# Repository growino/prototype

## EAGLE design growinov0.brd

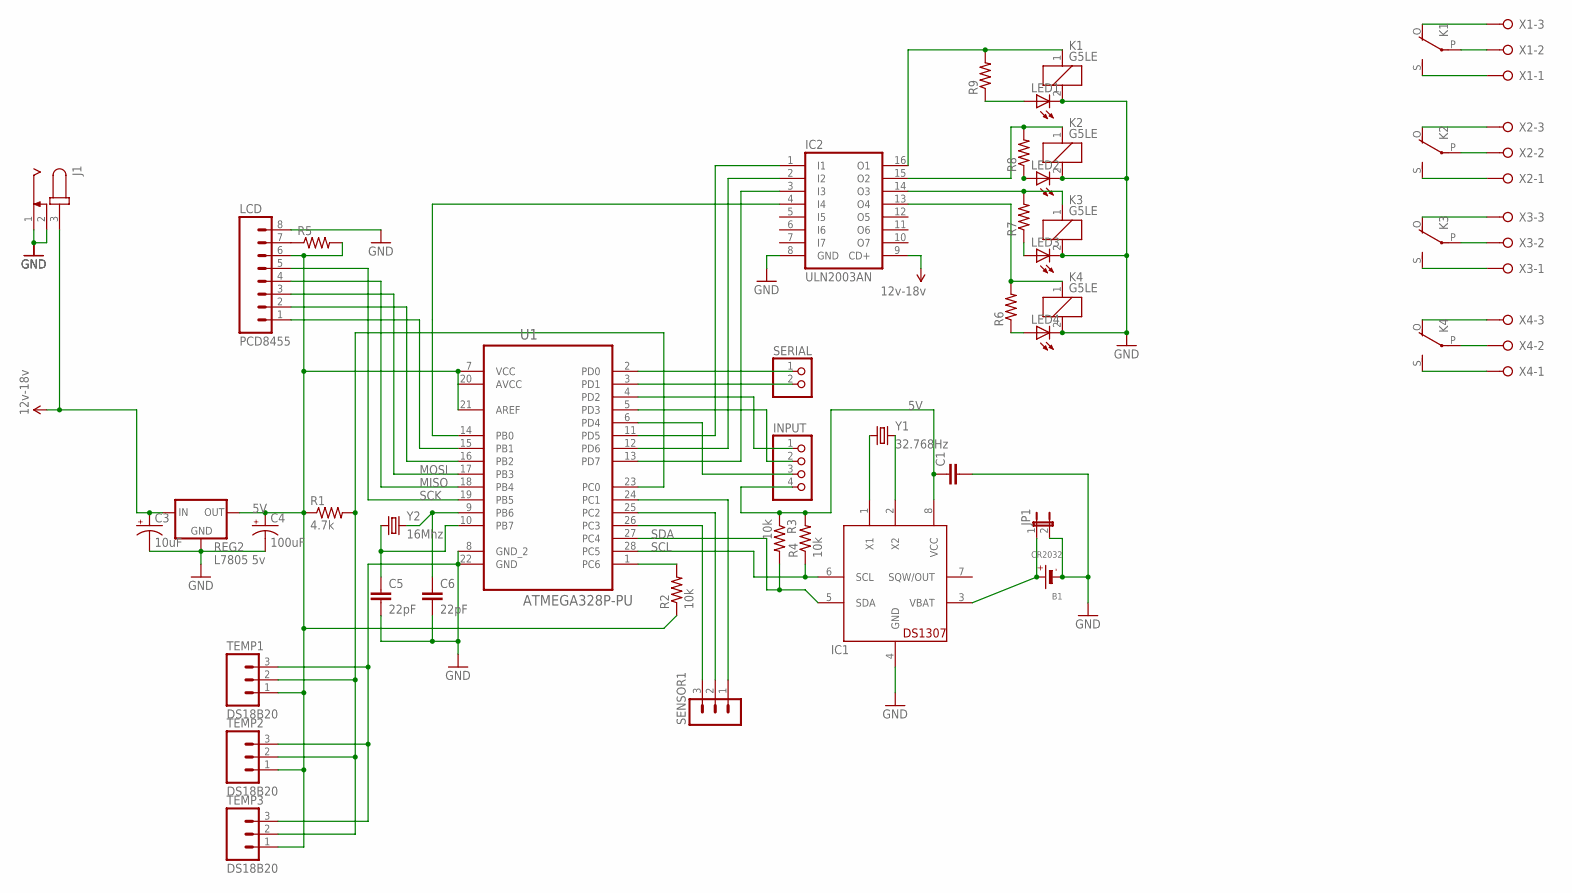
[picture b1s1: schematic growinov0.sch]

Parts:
B1: CR2032
C1: CAPPTH1; CAP-PTH-5MM
C3: 10uF; CPOL-RADIAL-10UF-25V
C4: 100uF; CPOL-RADIAL-100UF-25V
C5, C6: 22pF; CAP-PTH-SMALL-KIT
IC1: DS1307; DIL08
IC2: ULN2003AN; DIL16
INPUT: PINHD-1X4; 1X04
J1: JACK-PLUG0; SPC4077
JP1: JUMPER-2PTH; 1X02
K1, K2, K3, K4: G5LE
LCD: PCD8455; 1X08
LED1, LED2, LED3, LED4: LED3MM
R1: 4.7k; AXIAL-0.4
R2, R3, R4: 10k; AXIAL-0.4
R5, R6, R7, R8, R9: RESISTORPTH-1/4W-VERT; AXIAL-0.1
REG2: L7805 5v; 78XXL
SENSOR1: MA03-1
SERIAL: PINHD-1X2; 1X02
TEMP1, TEMP2, TEMP3: DS18B20; MOLEX-1X3
U1: ATMEGA328P-PU; DIP254P762X457-28
X1, X2, X3, X4: W237-3E
Y1: 32.768Hz; TC26H
Y2: 16Mhz; HC49US

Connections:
5V: C1.1, C4.1 (+), IC1.8 (VCC), INPUT.4, LCD.6, R1.P$1 (1), R2.P$1 (1), R3.P$1 (1), R4.P$2 (2), R5.P$2 (2), REG2.OUT, TEMP1.1, TEMP2.1, TEMP3.1, U1.7 (VCC), U1.20 (AVCC), U1.21 (AREF)
GND: B1.-, C1.2, C3.2 (-), C4.2 (-), C5.2, C6.2, IC1.4 (GND), IC2.8 (GND), J1.1, J1.2, JP1.2, K1.2, K2.2, K3.2, K4.2, LCD.8, LED1.K (C), LED2.K (C), LED3.K (C), LED4.K (C), REG2.GND, TEMP1.3, TEMP2.3, TEMP3.3, U1.8 (GND_2), U1.22 (GND)
MISO: LCD.4, U1.18 (PB4)
MOSI: LCD.3, U1.17 (PB3)
unnamed: B1.+, IC1.3 (VBAT), JP1.1
unnamed: R1.P$2 (2), TEMP1.2, TEMP2.2, TEMP3.2, U1.23 (PC0)
unnamed: IC1.1 (X1), Y1.1
unnamed: IC1.2 (X2), Y1.2
unnamed: R2.P$2 (2), U1.1 (PC6)
unnamed: K1.O, X1.3
unnamed: IC2.1 (I1), U1.11 (PD5)
unnamed: IC2.2 (I2), U1.12 (PD6)
unnamed: IC2.3 (I3), U1.13 (PD7)
unnamed: IC2.4 (I4), U1.14 (PB0)
unnamed: K1.S, X1.1
unnamed: C6.1, U1.9 (PB6), Y2.2
unnamed: C5.1, U1.10 (PB7), Y2.1
unnamed: LCD.2, U1.16 (PB2)
unnamed: LCD.1, U1.15 (PB1)
unnamed: IC2.16 (O1), K1.1, R9.P$2 (2)
unnamed: IC2.15 (O2), K2.1, R8.P$2 (2)
unnamed: IC2.14 (O3), K3.1, R7.P$2 (2)
unnamed: IC2.13 (O4), K4.1, R6.P$2 (2)
unnamed: K1.P, X1.2
unnamed: K4.O, X4.3
unnamed: K4.P, X4.2
unnamed: K4.S, X4.1
unnamed: K3.S, X3.1
unnamed: K3.P, X3.2
unnamed: K3.O, X3.3
unnamed: K2.S, X2.1
unnamed: K2.P, X2.2
unnamed: K2.O, X2.3
unnamed: SERIAL.1, U1.2 (PD0)
unnamed: SERIAL.2, U1.3 (PD1)
unnamed: INPUT.1, U1.4 (PD2)
unnamed: INPUT.2, U1.5 (PD3)
unnamed: INPUT.3, U1.6 (PD4)
unnamed: SENSOR1.1, U1.24 (PC1)
unnamed: SENSOR1.2, U1.25 (PC2)
unnamed: SENSOR1.3, U1.26 (PC3)
unnamed: LCD.7, R5.P$1 (1)
unnamed: LED2.A, R8.P$1 (1)
unnamed: LED4.A, R6.P$1 (1)
unnamed: LED3.A, R7.P$1 (1)
unnamed: LED1.A, R9.P$1 (1)
SCK: LCD.5, U1.19 (PB5)
SCL: IC1.6 (SCL), R4.P$1 (1), U1.28 (PC5)
SDA: IC1.5 (SDA), R3.P$2 (2), U1.27 (PC4)
VIN: C3.1 (+), IC2.9 (CD+), J1.3, REG2.IN

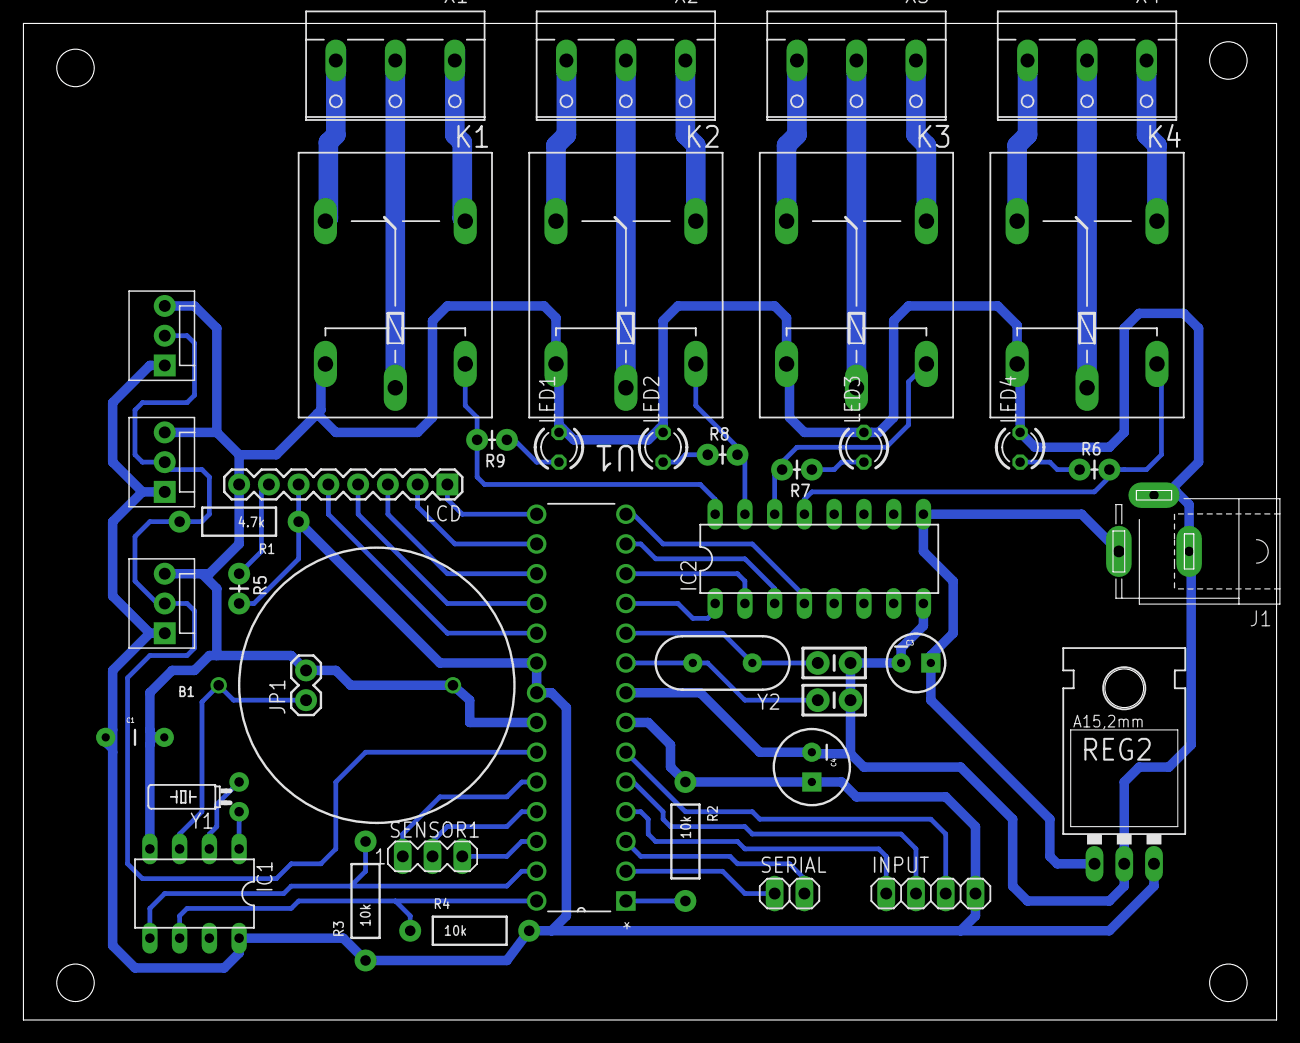
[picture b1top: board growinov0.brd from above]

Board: 2 copper layers, 107.0 x 85.1 mm, 42 parts (0 on the bottom side), 50 nets.

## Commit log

2014-11-02 Initial upload

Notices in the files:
parts and their libraries:
microbuilder: This work is placed in the public domain, and may be freely used for commercial and non-commercial work with the following conditions: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
SparkFun-Connectors: Licensing: Creative Commons ShareAlike 4.0 International - https://creativecommons.org/licenses/by-sa/4.0
